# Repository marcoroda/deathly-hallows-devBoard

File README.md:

# deathly-hallows-devBoard
SAMD51 deathly hallows dev board.

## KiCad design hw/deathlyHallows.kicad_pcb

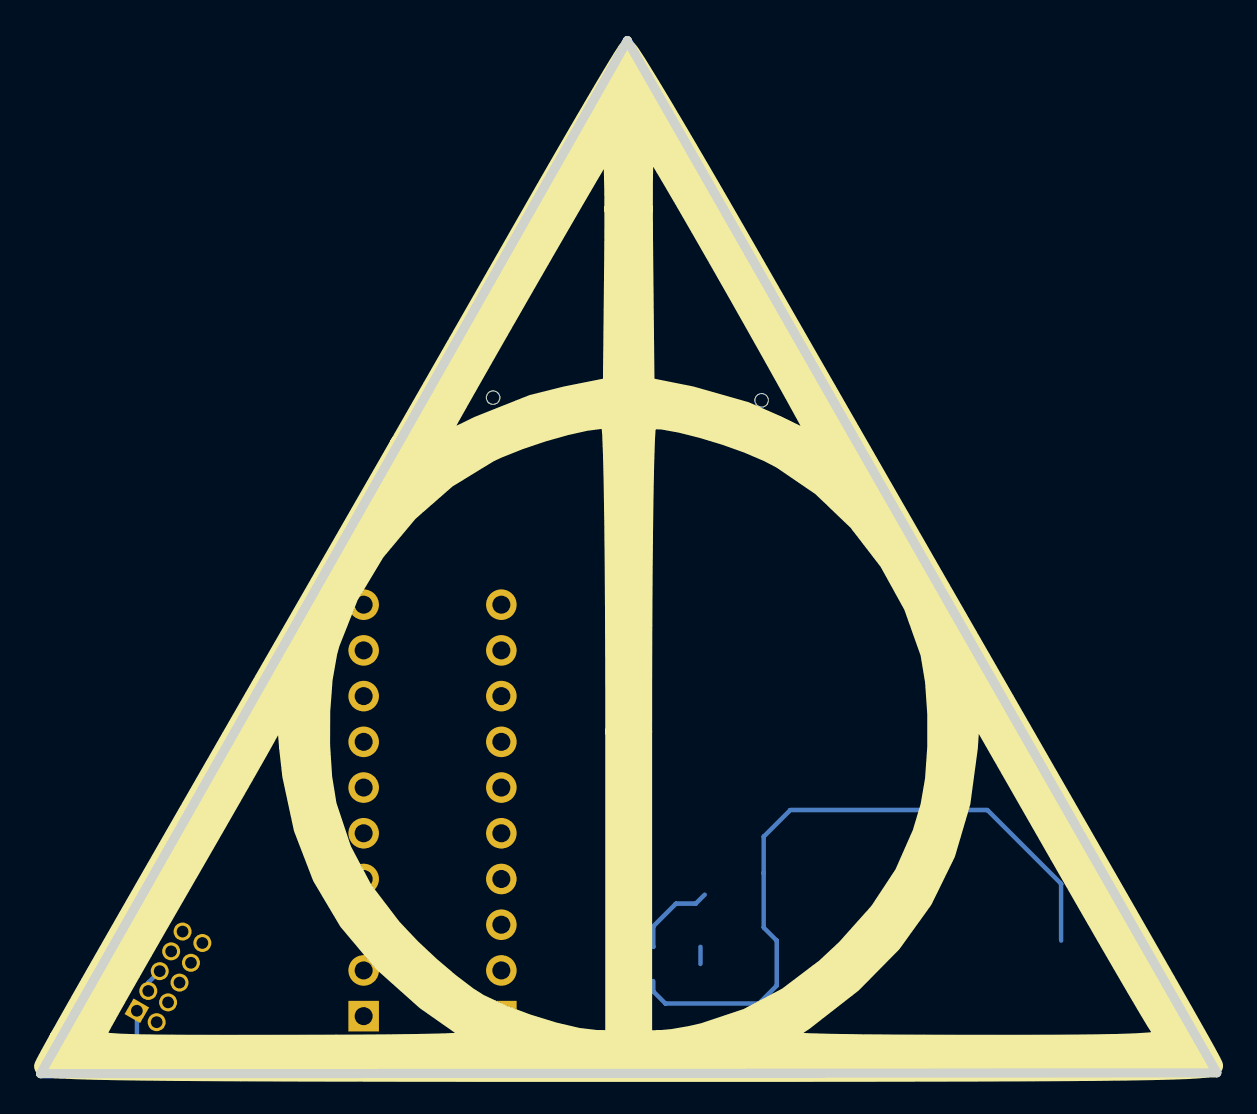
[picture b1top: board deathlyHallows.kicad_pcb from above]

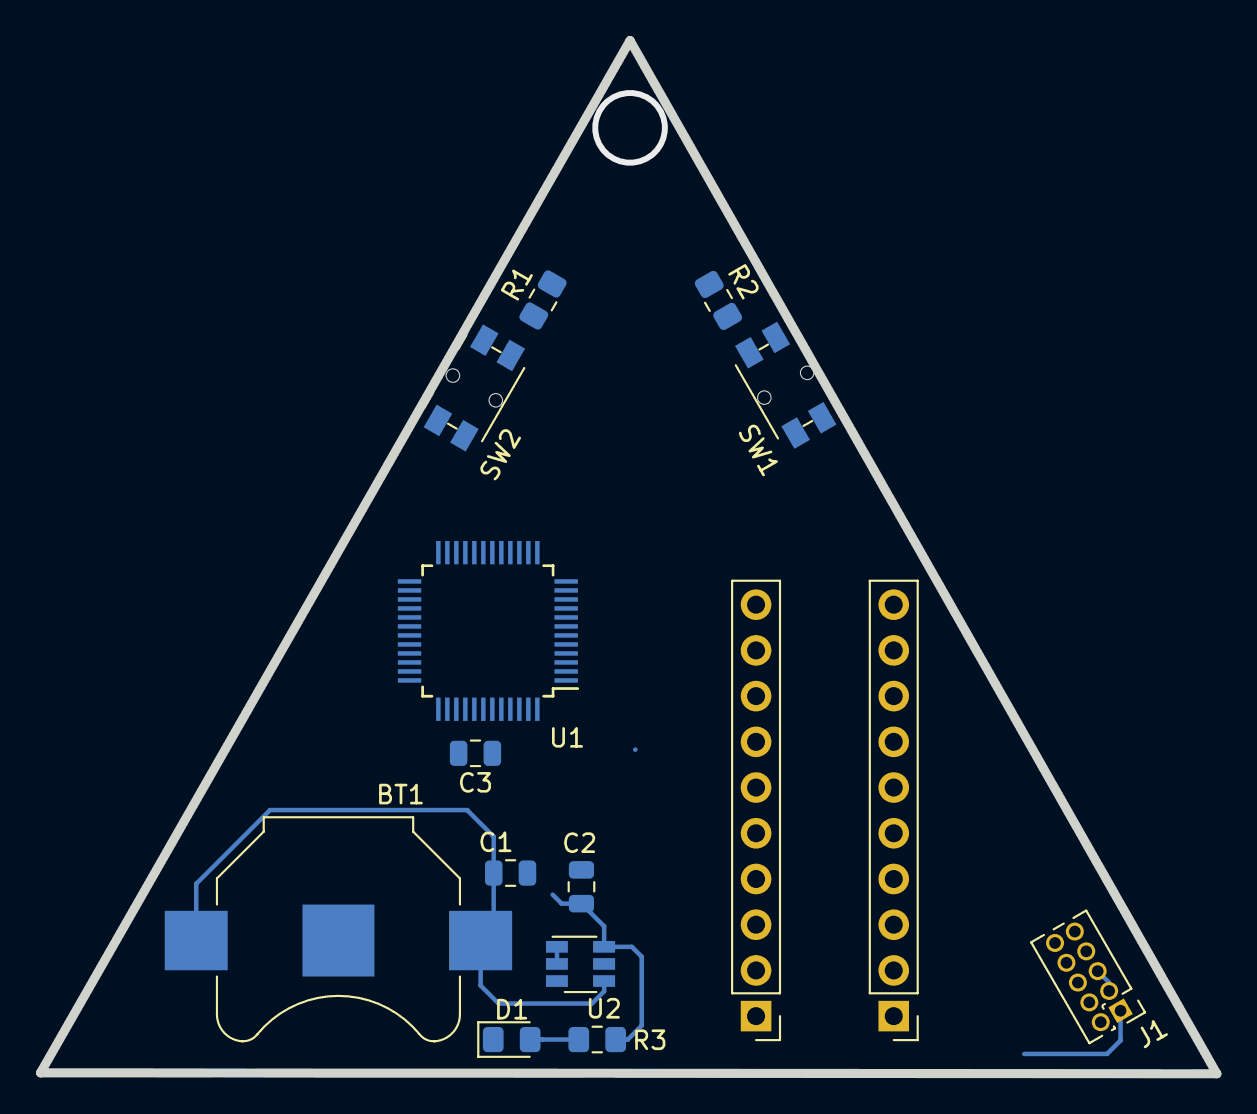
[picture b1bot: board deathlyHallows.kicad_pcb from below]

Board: 2 copper layers, 65.4 x 57.4 mm, 15 parts (15 on the bottom side), 10 nets.

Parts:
BT1: Battery_Cell; BatteryHolder_Keystone_3000_1x12mm
C1, C2, C3: 1uF; C_0805_2012Metric
D1: LED; LED_0805_2012Metric_Pad1.15x1.40mm_HandSolder
J1: Conn_ARM_JTAG_SWD_10; PinHeader_2x05_P1.27mm_Vertical
J2, J3: Conn_01x10; PinHeader_1x10_P2.54mm_Vertical
R1, R2: 10k; R_0805_2012Metric_Pad1.15x1.40mm_HandSolder
R3: 680; R_0805_2012Metric_Pad1.15x1.40mm_HandSolder
SW1, SW2: SW_Push; Panasonic_EVQPUM_EVQPUD
U1: ATSAMD21G18A-AUT; TQFP-48_7x7mm_P0.5mm
U2: LT1790-2.5; TSOT-23-6

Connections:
BTN: R1.1, SW2.2
GND: BT1.2, C1.2, C2.1, C3.2, D1.1, J1.3, J1.5, R1.2, SW1.1, U1.5, U1.18, U1.35, U1.42, U2.1, U2.2
unnamed: C3.1, U1.43
unnamed: D1.2, R3.2
RESET: J1.10, U1.40
RST: R2.1, SW1.2
SWDCLK: J1.4, U1.45
SWDIO: J1.2, U1.46
VDD: C2.2, J1.1, R2.2, R3.1, SW2.1, U1.6, U1.17, U1.36, U1.44, U2.6
VIN: BT1.1, C1.1, U2.4

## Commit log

2019-06-04 Initial draft.
2019-06-04 Added battery and LDO.
